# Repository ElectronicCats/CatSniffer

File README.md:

# CatSniffer

<p align=center><b>Where to buy and learn more</b></p>
<p align=center>

</p>

<p align=center>
  
</p>

CatSniffer :smirk_cat: is an original multiprotocol, and multiband board made for sniffing, communicating, and attacking IoT (Internet of Things) devices. It was designed as a highly portable USB stick that integrates the new chips TI CC1352, Semtech SX1262, and an RP2040 for V3 or a Microchip SAMD21E17 for V2.

This board is a swiss army knife for IoT security researchers, developers, and enthusiasts. The board can be used with different types of software including third-party sniffers such as [SmartRF Packet Sniffer](https://www.ti.com/tool/PACKET-SNIFFER), [Sniffle](https://github.com/ElectronicCats/Sniffle), [zigbee2mqtt](https://github.com/Koenkk/zigbee2mqtt), [Z-Stack-firmware](https://github.com/Koenkk/Z-Stack-firmware), [Ubiqua Protocol Analyzer](https://www.ubilogix.com/ubiqua/), [our custom software](https://github.com/ElectronicCats/CatSniffer-Tools), or you can even write your own software for your specific needs.

CatSniffer can operate in 3 different technologies:
* LoRa
* Sub 1 GHz
* 2.4 GHz

This work was inspired by our friend's work [Michael Ossmann](https://twitter.com/michaelossmann) as a tribute to his outstanding job in [Greatscott Gadgets](https://greatscottgadgets.com/), making devices like the YardStick, GreatFET, HackRF, and Ubertooth.

## Versions

The CatSniffer has been evolving since its first release:

- CatSniffer v1.2
- CatSniffer v1.3
- CatSniffer v2.0
- CatSniffer v2.1
- CatSniffer v3.1

We as an pro-open-source companies decided to keep the support for each version, but having in mind that newer versions will have more features than the first versions.

The different firmwares are inside the repository and not in the realese section to keep a propper track of the compiled and source files.

## Protocols
- Thread
- Zigbee
- Bluetooth 5 Low Energy (BLE)
- IEEE 802.15.4g
- 6LoWPAN (IPv6 over Low power Wireless Personal Area Networks)
- Sub 1Ghz and patented systems
- LoRa/LoRaWAN
- Wi-SUN
- Amazon Sidewalk
- mioty®

## Features
- "The SimpleLink™ [CC1352P1F3RGZ](https://www.ti.com/lit/ds/symlink/cc1352p.pdf?ts=1631314674885) device is a multiprotocol and multi-band Sub-1 GHz and 2.4-GHz wireless microcontroller (MCU) supporting Thread, Zigbee®, Bluetooth® 5.2 Low Energy, IEEE 802.15.4g, IPv6-enabled smart objects (6LoWPAN), MIOTY®, Wi-SUN®, proprietary systems".
- CatSniffer uses Microchip SAMD21E17 (V2 or previous) and RP2040 (V3 or later) as a USB-UART bridge to communicate with the CC1352 chip; it's not necessary for a manual driver installation (exceptions could exist).
- Compatible OS: Windows and Linux.
- Auto program through the bootloader from TI CC (as long as it's not disabled in the code). No need for an external programmer, and it can be debugged with cJTAG through the default pin.
- Antenna SMA port for an Antenna of your choice.
- LEDs of general-purpose.
- Reset button for RP2040, SAMD21 & CC1352, Boot of CC1352, and one more for general purpose.

## Wiki and Getting Started

[Getting Started in our Wiki](https://github.com/ElectronicCats/CatSniffer/wiki)

## Firmware Repository
All Catsniffer Firmware has been moved to a different repository, to have a better version control, and issue tracking you will find it here:

https://github.com/ElectronicCats/CatSniffer-Firmware

All catsniffer versions are supported in this repository, you will need to check what version you own and select the proper branch to develop or release for just program your board.

## Software Repository
All Catsniffer Software has been moved to a different repository, to have a better version control, and issue tracking you will find it here:

https://github.com/ElectronicCats/CatSniffer-Tools

## Compatible Software
* [Smart RF Packet Sniffer 2](https://github.com/ElectronicCats/CatSniffer/wiki/06.-Supported-Software#smart-rf-packet-sniffer-2)
* [Wireshark](https://github.com/ElectronicCats/CatSniffer/wiki/06.-Supported-Software#wireshark)
* [pycatsniffer tool (BETA)](https://github.com/ElectronicCats/CatSniffer/wiki/06.-Supported-Software#pycatsniffer-tool)
* [Sniffle](https://github.com/ElectronicCats/CatSniffer/wiki/06.-Supported-Software#sniffle)
* [Ubiqua Protocol Analyzer](https://github.com/ElectronicCats/CatSniffer/wiki/06.-Supported-Software#ubiqua-protocol-analyzer)
* [zigbee2mqtt](https://github.com/Koenkk/zigbee2mqtt)
* [Z-Stack-firmware](https://github.com/Koenkk/Z-Stack-firmware)

## Pre-requisites for building firmware
* Arduino IDE for RP2040 or SAMD21E17
* CCS version: The packet sniffer firmware has been tested with CCS 10.2
* SimpleLink CC13x2 and CC26x2 SDK 
* Python 3

## Note
This kit is designed to allow Product developers to evaluate electronic components, circuit, or software associated with the kit to determine whether to incorporate such items in a finished product and Software developers to write software applications for use with the end product. This kit is a developer product and when assembled may not be resold or otherwise marketed unless all required FCC (or any other local authority) equipment authorizations are first obtained. Operation is subject to the condition that this product not cause harmful interference to licensed radio stations and that this product accept harmful interference.

## Workshops

We have been doing worshops held in different security related events the material avaible is public and can be found [here](https://drive.google.com/drive/folders/1SxkF2-uWVFw2BZa5lym5f42ivyW23bVV)

## How to contribute 
 Contributions are welcome! 

Please read the document  [**Contribution Manual**](https://github.com/ElectronicCats/electroniccats-cla/blob/main/electroniccats-contribution-manual.md)  which will show you how to contribute your changes to the project.

✨ Thanks to all our [contributors](https://github.com/ElectronicCats/CatSniffer/graphs/contributors)! ✨

See [**_Electronic Cats CLA_**](https://github.com/ElectronicCats/electroniccats-cla/blob/main/electroniccats-cla.md) for more information.

See the  [**community code of conduct**](https://github.com/ElectronicCats/electroniccats-cla/blob/main/electroniccats-community-code-of-conduct.md) for a vision of the community we want to build and what we expect from it.

## License

Electronic Cats invests time and resources providing this open source design, please support Electronic Cats and open-source hardware by purchasing products from Electronic Cats!

Designed by Electronic Cats.

Firmware released under an GNU AGPL v3.0 license. See the LICENSE file for more information.

Hardware released under an CERN Open Hardware [Licence v1.2](https://github.com/ElectronicCats/CatSniffer/blob/master/LICENSE.md) See the LICENSE_HARDWARE file for more.
Electronic Cats is a registered trademark, please do not use if you sell these PCBs.

3 April 2021

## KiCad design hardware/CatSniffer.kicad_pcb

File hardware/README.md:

# Hardware

- Schematic
- PCB Gerbers
- Hardware Libraries

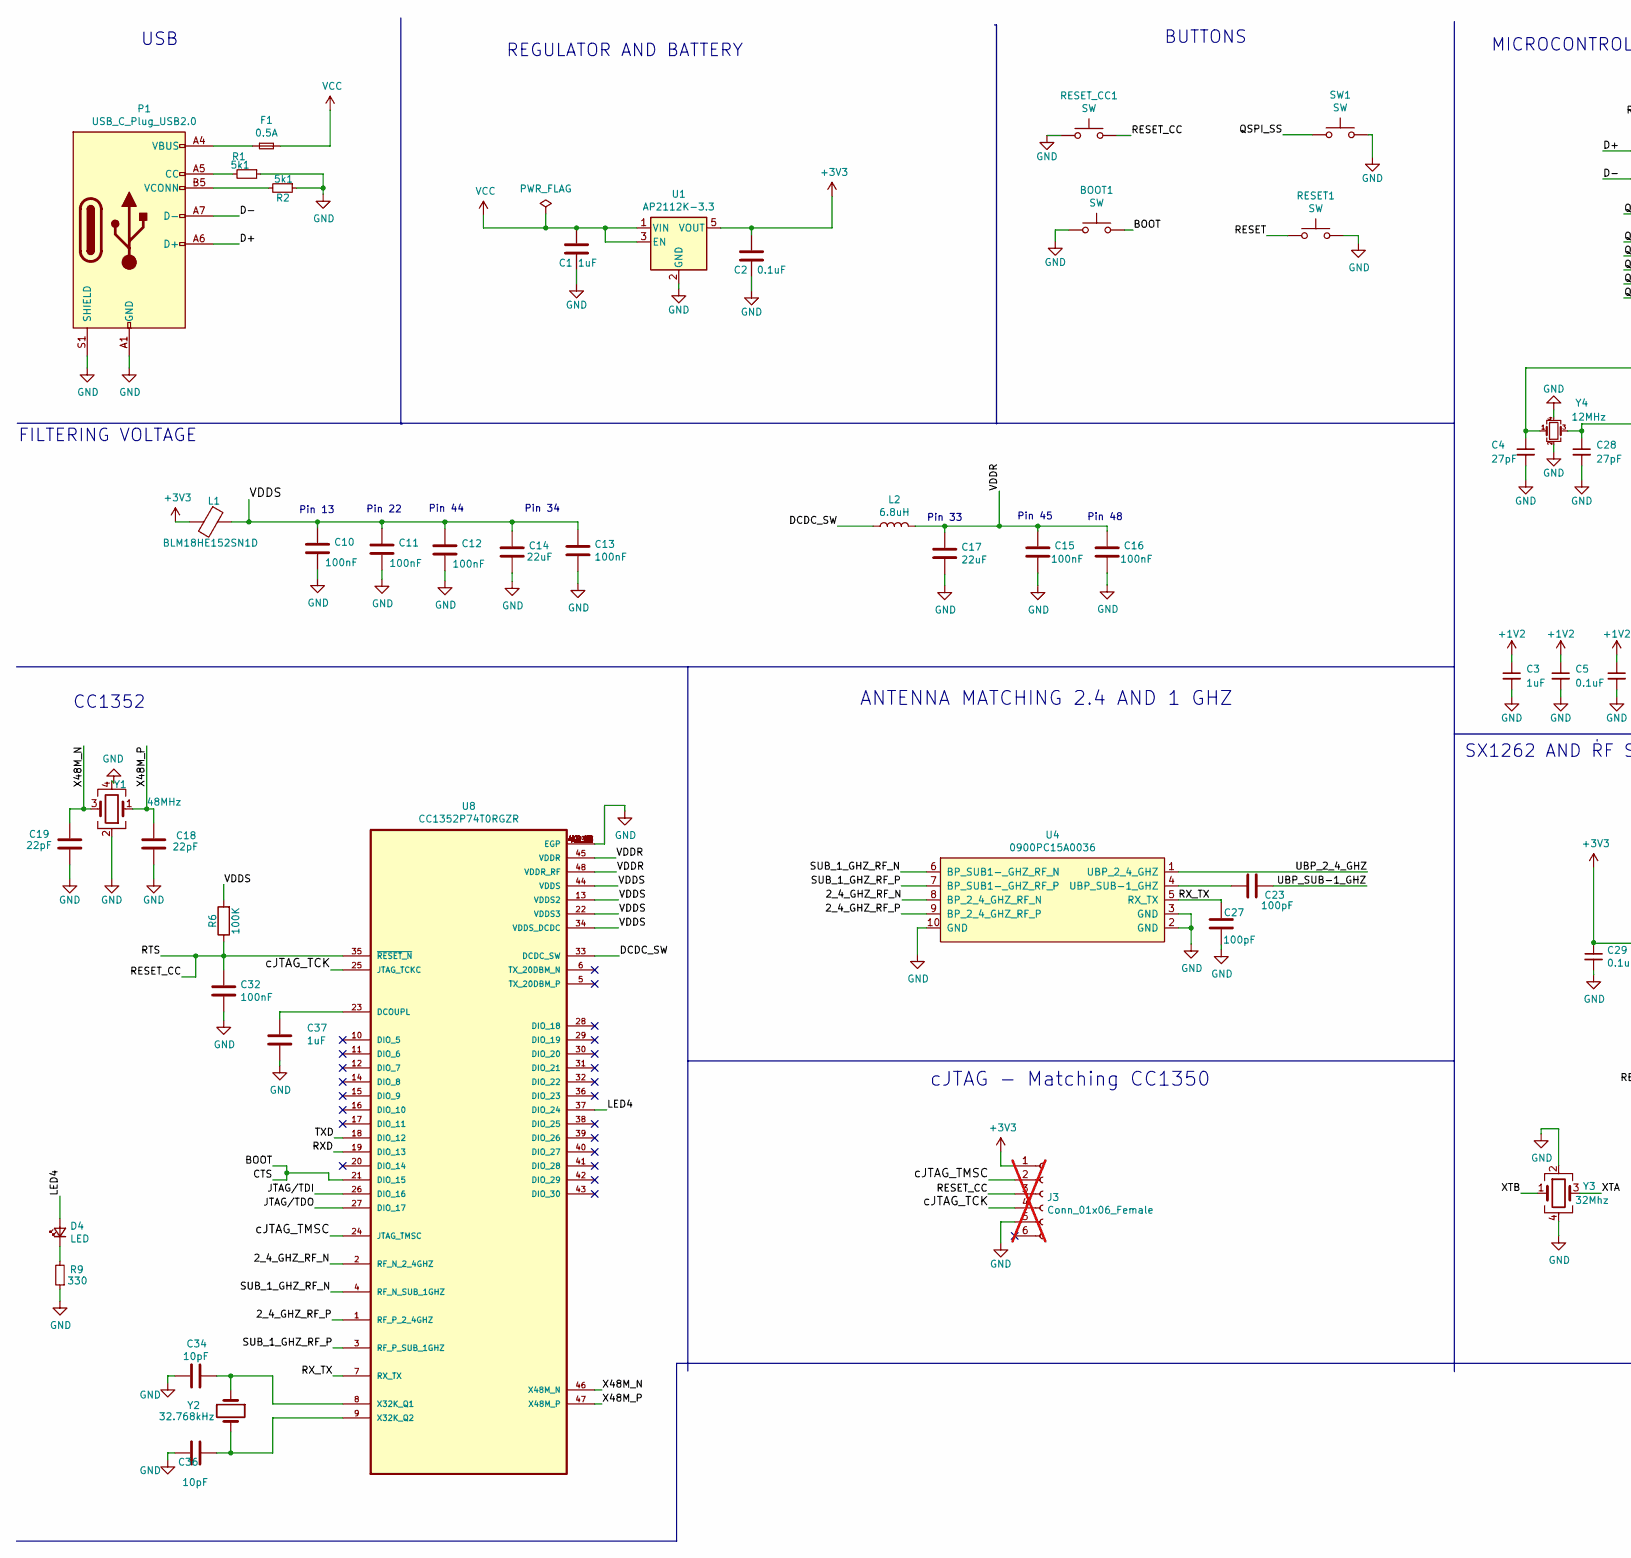
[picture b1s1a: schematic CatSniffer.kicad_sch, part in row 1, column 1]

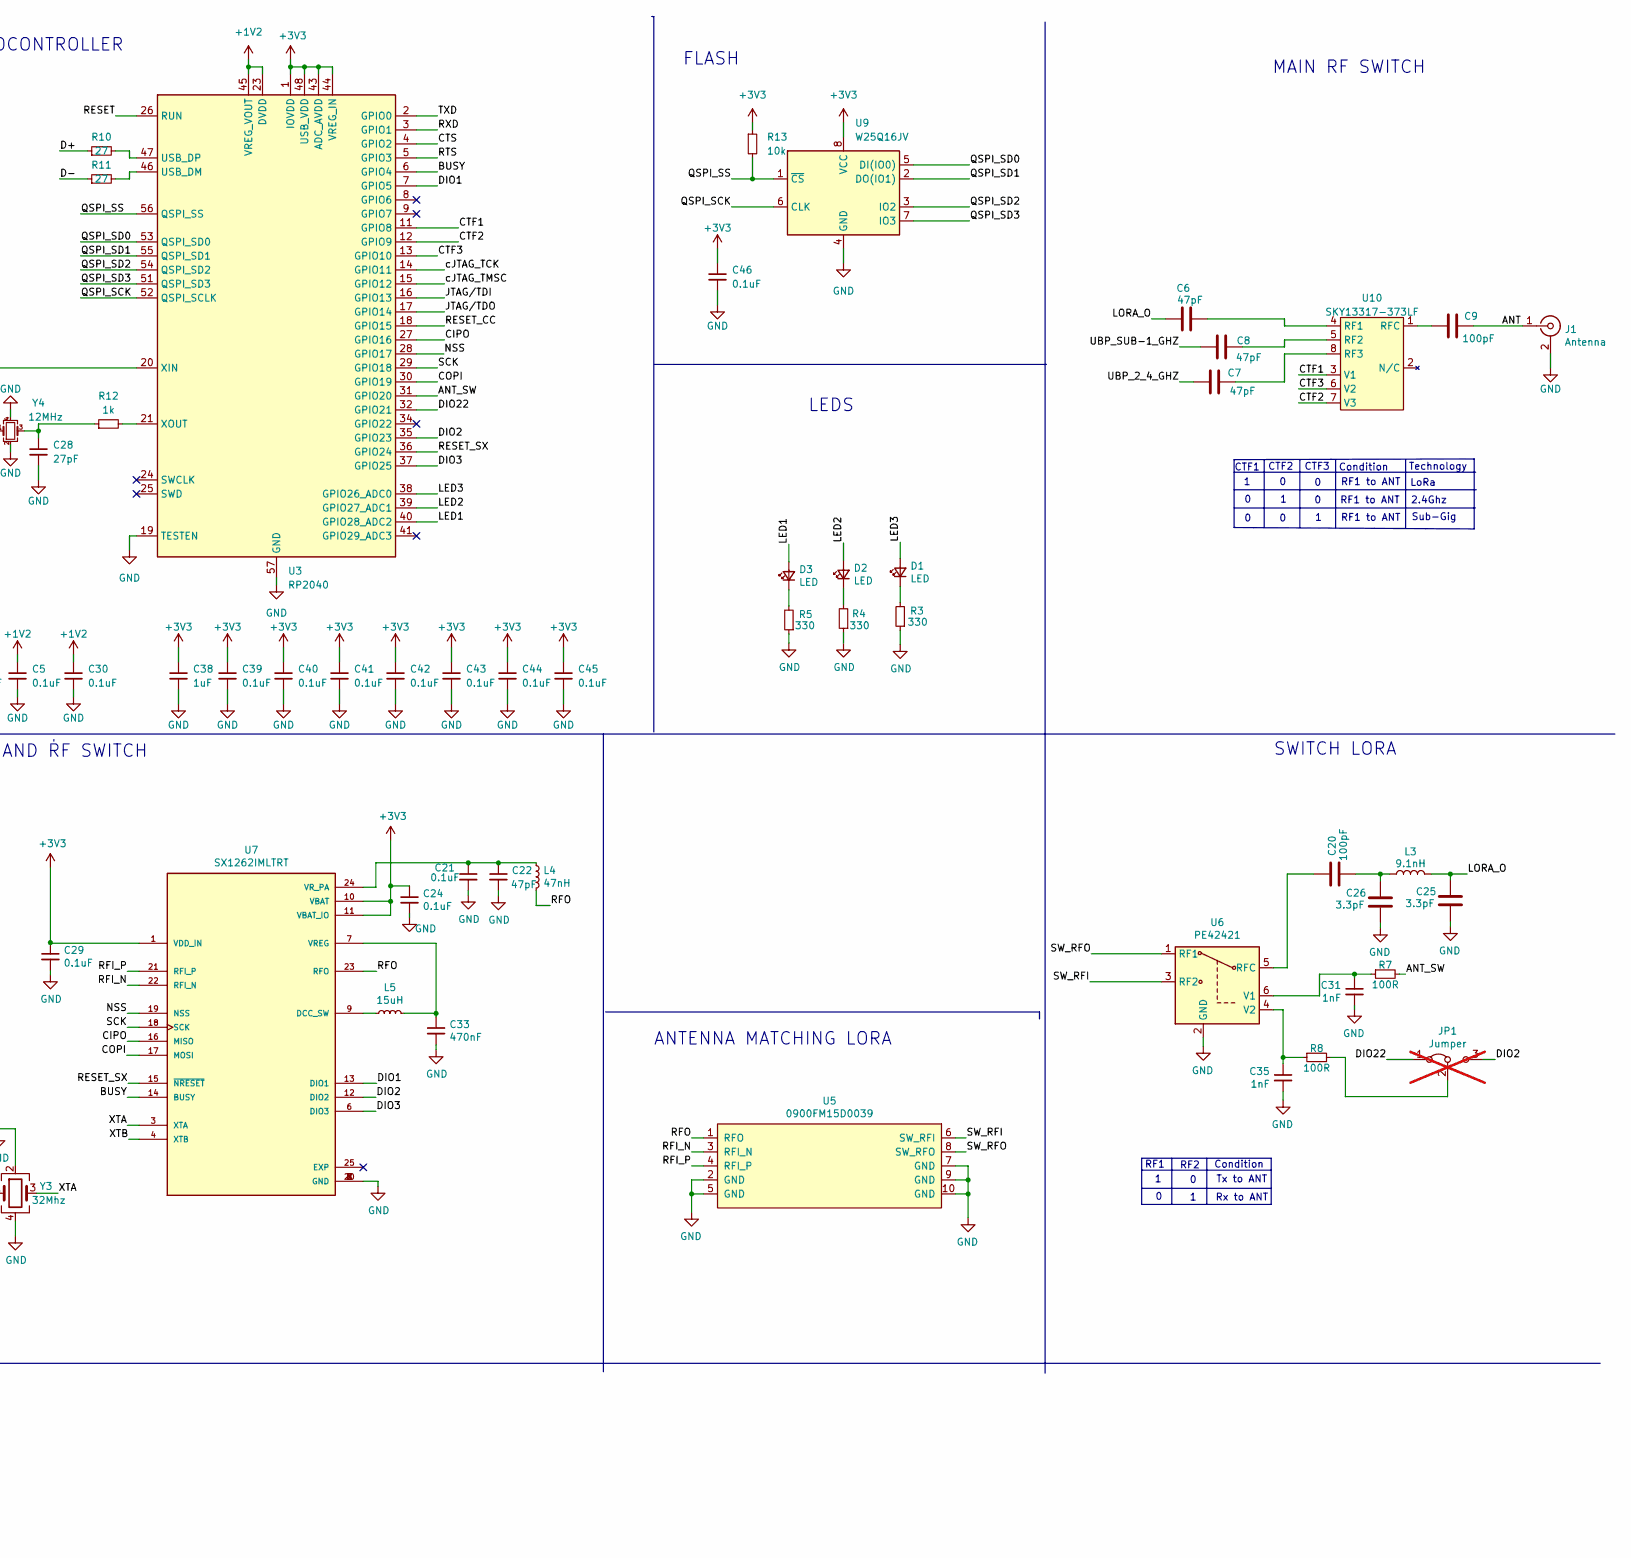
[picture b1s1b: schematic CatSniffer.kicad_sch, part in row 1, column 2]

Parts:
BOOT1: SW; TS1088R02026; LCSC# C455281
C1, C37: 1uF; C_0603_1608Metric; LCSC# C108343
C2, C21, C24, C29: 0.1uF; C_0603_1608Metric; LCSC# C14663
C3, C38: 1uF; C_0402_1005Metric; Mouser# 963-MSRLJ103SB5105MF
C4, C28: 27pF; C_0402_1005Metric; Mouser# 81-GJM1555C1H270FB1D
C5, C30, C39, C40, C41, C42, C43, C44, C45, C46: 0.1uF; C_0402_1005Metric; Mouser# 963-MSAST105SB7104KF
C6, C7, C8, C22: 47pF; C_0603_1608Metric; LCSC# C519486
C9, C20, C23, C27: 100pF; C_0603_1608Metric; LCSC# C14858
C10, C11, C12, C13, C15, C16, C32: 100nF; C_0402_1005Metric; LCSC# C162179
C14, C17: 22uF; C_0603_1608Metric; LCSC# C109447
C18, C19: 22pF; C_0603_1608Metric; LCSC# C170132
C25, C26: 3.3pF; C_0603_1608Metric; LCSC# C162225
C31, C35: 1nF; C_0603_1608Metric; LCSC# C1588
C33: 470nF; C_0603_1608Metric; LCSC# C170149
C34, C36: 10pF; C_0603_1608Metric; LCSC# C472782
D1, D2, D3, D4: LED; LED_0603_1608Metric_Pad1.05x0.95mm_HandSolder; LCSC# C524045
F1: 0.5A; Fuse_0805_2012Metric_Pad1.15x1.40mm_HandSolder; Mouser# 594-MFU0805FF00500P1
J1: Antenna; SMA_EDGE; LCSC# C530661
J3: Conn_01x06_Female; Tag-Connect_TC2030-IDC-NL_2x03_P1.27mm_Vertical; not fitted
JP1: Jumper; SolderJumper-3_P1.3mm_Bridged12_RoundedPad1.0x1.5mm_NumberL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; not fitted
L1: BLM18HE152SN1D; L_0603_1608Metric; Mouser# BLM18HE152SN1D
L2: 6.8uH; L_0603_1608Metric; Mouser# MLZ1608M6R8WT000
L3: 9.1nH; L_0603_1608Metric; LCSC# C395094
L4: 47nH; L_0603_1608Metric; LCSC# C578001
L5: 15uH; L_0603_1608Metric; LCSC# C57838
P1: USB_C_Plug_USB2.0; C393939; LCSC# C709357
R1, R2: 5k1; R_0603_1608Metric; LCSC# C319561
R3, R4, R5, R9: 330; R_0603_1608Metric; LCSC# C408915
R6: 100K; R_0603_1608Metric; LCSC# C179820
R7, R8: 100R; R_0603_1608Metric; LCSC# C700506
R10, R11: 27; R_0402_1005Metric; Mouser# 755-ESR01MZPF27R0
R12: 1k; R_0402_1005Metric; Mouser# 594-MCS0402MD1001DE0
R13: 10k; R_0402_1005Metric; Mouser# 594-MCS04020D1002BE0
RESET1: SW; TS1088R02026; LCSC# C455281
RESET_CC1: SW; TS1088R02026; LCSC# C455281
SW1: SW; TS1088R02026; LCSC# C455281
U1: AP2112K-3.3; SOT-23-5; Mouser# 865-XC6210B332MR-G
U3: RP2040; QFN-56-1EP_7x7mm_P0.4mm_EP3.2x3.2mm; LCSC# C2040
U4: 0900PC15A0036; 0900FM15D0039E; Mouser# 609-0900PC15A0036E
U5: 0900FM15D0039; 0900FM15D0039E; Mouser# 609-0900FM15D0039E
U6: PE42421; SOT-363_SC-70-6; Mouser# 81-PE42421SCAA-Z
U7: SX1262IMLTRT; QFN-24-1EP_4x4mm_P0.5mm_EP2.65x2.65mm; Mouser# 947-SX1262IMLTRT
U8: CC1352P74T0RGZR; VQFN-48-1EP_7x7mm_P0.5mm_EP5.15x5.15mm_ThermalVias; Mouser# 595-CC1352P1F3RGZT
U9: W25Q16JV; W25Q16JVUUIQ; Mouser# 454-W25Q16JVUUIQTR
U10: SKY13317-373LF; LCSC# C129190
Y1: 48MHz; Crystal_SMD_3225-4Pin_3.2x2.5mm; LCSC# C389928
Y2: 32.768kHz; Crystal_SMD_2012-2Pin_2.0x1.2mm; LCSC# C97603
Y3: 32Mhz; Crystal_SMD_2520-4Pin_2.5x2.0mm; LCSC# C255969
Y4: 12MHz; Crystal_SMD_3225-4Pin_3.2x2.5mm; LCSC# C2848217

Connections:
+1V2: C3.1, C5.1, C30.1, U3.23 (DVDD), U3.45 (VREG_VOUT), U3.50 (DVDD)
+3V3: C2.2, C24.1, C29.1, C38.1, C39.1, C40.1, C41.1, C42.1, C43.1, C44.1, C45.1, C46.1, J3.1, L1.2, R13.1, U1.5 (VOUT), U3.1 (IOVDD), U3.10 (IOVDD), U3.22 (IOVDD), U3.33 (IOVDD), U3.42 (IOVDD), U3.43 (ADC_AVDD), U3.44 (VREG_IN), U3.48 (USB_VDD), U3.49 (IOVDD), U7.1 (VDD_IN), U7.10 (VBAT), U7.11 (VBAT_IO), U9.8 (VCC)
/2_4_GHZ_RF_N: U4.8 (BP_2_4_GHZ_RF_N), U8.2 (RF_N_2_4GHZ)
/2_4_GHZ_RF_P: U4.9 (BP_2_4_GHZ_RF_P), U8.1 (RF_P_2_4GHZ)
/ANT: C9.2, J1.1 (In)
/ANT_SW: R7.2, U3.31 (GPIO20)
/BOOT: BOOT1.2, U3.4 (GPIO2), U8.21 (DIO_15)
/BUSY: U3.6 (GPIO4), U7.14 (BUSY)
/CIPO: U3.27 (GPIO16), U7.16 (MISO)
/COPI: U3.30 (GPIO19), U7.17 (MOSI)
/CTF1: U3.11 (GPIO8), U10.3 (V1)
/CTF2: U3.12 (GPIO9), U10.7 (V3)
/CTF3: U3.13 (GPIO10), U10.6 (V2)
/D+: P1.A6 (D+), R10.1
/D-: P1.A7 (D-), R11.1
/DCDC_SW: L2.1, U8.33 (DCDC_SW)
/DIO1: U3.7 (GPIO5), U7.13 (DIO1)
/DIO2: JP1.3 (B), U3.35 (GPIO23), U7.12 (DIO2)
/DIO3: U3.37 (GPIO25), U7.6 (DIO3)
/DIO22: JP1.1 (A), U3.32 (GPIO21)
/JTAG/TDI: U3.16 (GPIO13), U8.26 (DIO_16)
/JTAG/TDO: U3.17 (GPIO14), U8.27 (DIO_17)
/LED1: D3.2 (A), U3.40 (GPIO28_ADC2)
/LED2: D2.2 (A), U3.39 (GPIO27_ADC1)
/LED3: D1.2 (A), U3.38 (GPIO26_ADC0)
/LED4: D4.2 (A), U8.37 (DIO_24)
/LORA_O: C6.1, C25.1, L3.1
/NSS: U3.28 (GPIO17), U7.19 (NSS)
/QSPI_SCK: U3.52 (QSPI_SCLK), U9.6 (CLK)
/QSPI_SD0: U3.53 (QSPI_SD0), U9.5 (DI(IO0))
/QSPI_SD1: U3.55 (QSPI_SD1), U9.2 (DO(IO1))
/QSPI_SD2: U3.54 (QSPI_SD2), U9.3 (IO2)
/QSPI_SD3: U3.51 (QSPI_SD3), U9.7 (IO3)
/QSPI_SS: R13.2, SW1.1, U3.56 (QSPI_SS), U9.1 (~CS)
/RESET: RESET1.1, U3.26 (RUN)
/RESET_CC: C32.1, J3.3, R6.1, RESET_CC1.2, U3.5 (GPIO3), U3.18 (GPIO15), U8.35 (~RESET_N)
/RESET_SX: U3.36 (GPIO24), U7.15 (~NRESET)
/RFI_N: U5.3 (RFI_N), U7.22 (RFI_N)
/RFI_P: U5.4 (RFI_P), U7.21 (RFI_P)
/RFO: L4.2, U5.1 (RFO), U7.23 (RFO)
/RXD: U3.3 (GPIO1), U8.19 (DIO_13)
/RX_TX: C27.2, U4.5 (RX_TX), U8.7 (RX_TX)
/SCK: U3.29 (GPIO18), U7.18 (SCK)
/SUB_1_GHZ_RF_N: U4.6 (BP_SUB1-_GHZ_RF_N), U8.4 (RF_N_SUB_1GHZ)
/SUB_1_GHZ_RF_P: U4.7 (BP_SUB1-_GHZ_RF_P), U8.3 (RF_P_SUB_1GHZ)
/SW_RFI: U5.6 (SW_RFI), U6.3 (RF2)
/SW_RFO: U5.8 (SW_RFO), U6.1 (RF1)
/TXD: U3.2 (GPIO0), U8.18 (DIO_12)
/UBP_2_4_GHZ: C7.1, U4.1 (UBP_2_4_GHZ)
/UBP_SUB-1_GHZ: C8.1, C23.1
/VDDR: C15.1, C16.1, C17.1, L2.2, U8.45 (VDDR), U8.48 (VDDR_RF)
/VDDS: C10.1, C11.1, C12.1, C13.1, C14.1, L1.1, R6.2, U8.13 (VDDS2), U8.22 (VDDS3), U8.34 (VDDS_DCDC), U8.44 (VDDS)
/X48M_N: C19.1, U8.46 (X48M_N), Y1.3
/X48M_P: C18.1, U8.47 (X48M_P), Y1.1
/XTA: U7.3 (XTA), Y3.3
/XTB: U7.4 (XTB), Y3.1
/cJTAG_TCK: J3.4, U3.14 (GPIO11), U8.25 (JTAG_TCKC)
/cJTAG_TMSC: J3.2, U3.15 (GPIO12), U8.24 (JTAG_TMSC)
GND: BOOT1.1, C1.1, C2.1, C3.2, C4.2, C5.2, C10.2, C11.2, C12.2, C13.2, C14.2, C15.2, C16.2, C17.2, C18.2, C19.2, C21.2, C22.2, C24.2, C25.2, C26.2, C27.1, C28.2, C29.2, C30.2, C31.2, C32.2, C33.2, C34.2, C35.2, C36.2, C37.2, C38.2, C39.2, C40.2, C41.2, C42.2, C43.2, C44.2, C45.2, C46.2, J1.2 (Ext), J3.5, P1.A1 (GND), P1.A12 (GND), P1.B1 (GND), P1.B12 (GND), P1.S1 (SHIELD), R1.1, R2.1, R3.1, R4.1, R5.1, R9.1, RESET1.2, RESET_CC1.1, SW1.2, U1.2 (GND), U3.19 (TESTEN), U3.57 (GND), U4.2 (GND), U4.3 (GND), U4.10 (GND), U5.2 (GND), U5.5 (GND), U5.7 (GND), U5.9 (GND), U5.10 (GND), U6.2 (GND), U7.2 (GND), U7.5 (GND), U7.8 (GND), U7.20 (GND), U8.49 (EGP), U8.49_1 (EGP), U8.49_2 (EGP), U8.49_3 (EGP), U8.49_4 (EGP), U8.49_5 (EGP), U8.49_6 (EGP), U8.49_7 (EGP), U8.49_8 (EGP), U8.49_9 (EGP), U8.49_10 (EGP), U8.49_11 (EGP), U8.49_12 (EGP), U8.49_13 (EGP), U8.49_14 (EGP), U8.49_15 (EGP), U8.49_16 (EGP), U8.49_17 (EGP), U8.49_18 (EGP), U8.49_19 (EGP), U8.49_20 (EGP), U8.49_21 (EGP), U9.4 (GND), Y1.2, Y1.4, Y3.2, Y3.4, Y4.2, Y4.4
unnamed: C20.2, C26.1, L3.2
unnamed: C28.1, R12.1, Y4.3
unnamed: D1.1 (K), R3.2
unnamed: D2.1 (K), R4.2
unnamed: D3.1 (K), R5.2
unnamed: D4.1 (K), R9.2
unnamed: F1.1, P1.A4 (VBUS), P1.A9 (VBUS), P1.B4 (VBUS), P1.B9 (VBUS)
unnamed: JP1.2 (C), R8.2
unnamed: P1.A5 (CC), R1.2
unnamed: P1.B5 (VCONN), R2.2
unnamed: R11.2, U3.46 (USB_DM)
unnamed: R10.2, U3.47 (USB_DP)
unnamed: C4.1, U3.20 (XIN), Y4.1
unnamed: R12.2, U3.21 (XOUT)
unnamed: C23.2, U4.4 (UBP_SUB-1_GHZ)
unnamed: C20.1, U6.5 (RFC)
unnamed: C31.1, R7.1, U6.6 (V1)
unnamed: C35.1, R8.1, U6.4 (V2)
unnamed: L5.1, U7.9 (DCC_SW)
unnamed: C33.1, L5.2, U7.7 (VREG)
unnamed: C21.1, C22.1, L4.1, U7.24 (VR_PA)
unnamed: C37.1, U8.23 (DCOUPL)
unnamed: C34.1, U8.8 (X32K_Q1), Y2.1
unnamed: C36.1, U8.9 (X32K_Q2), Y2.2
unnamed: C6.2, U10.4 (RF1)
unnamed: C8.2, U10.5 (RF2)
unnamed: C7.2, U10.8 (RF3)
unnamed: C9.1, U10.1 (RFC)
VCC: C1.2, F1.2, U1.1 (VIN), U1.3 (EN)

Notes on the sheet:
RF1 to ANT
cJTAG - Matching CC1350
Rx to ANT
Pin 48
Pin 33
2.4Ghz
CTF2
REGULATOR AND BATTERY
ANTENNA MATCHING LORA
RF1
SWITCH LORA
ANTENNA MATCHING 2.4 AND 1 GHZ
Pin 34
Pin 45
CTF1
FILTERING VOLTAGE
Condition
Pin 44
Technology
FLASH
Pin 22
Tx to ANT
MAIN RF SWITCH
BUTTONS
Pin 13
CC1352
LoRa
CTF3
Sub-Gig
MICROCONTROLLER
USB
SX1262 AND RF SWITCH
LEDS
RF2

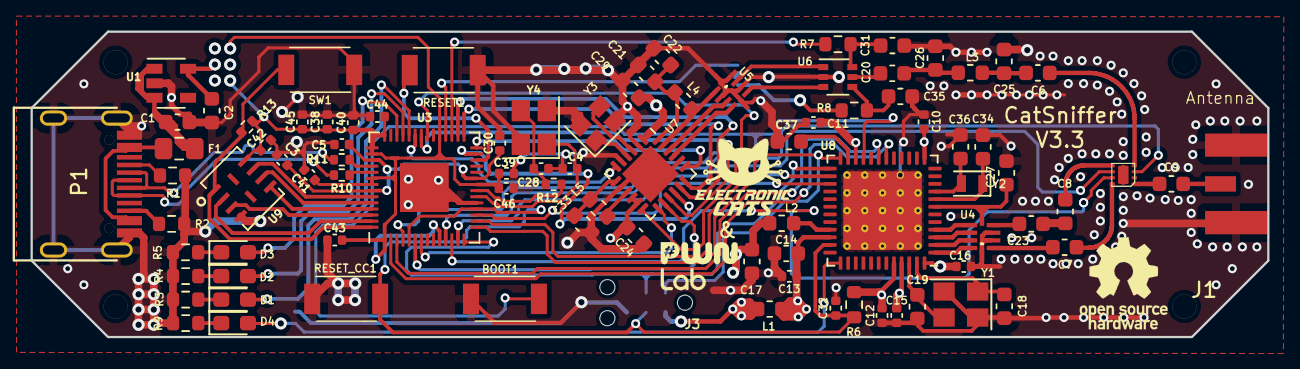
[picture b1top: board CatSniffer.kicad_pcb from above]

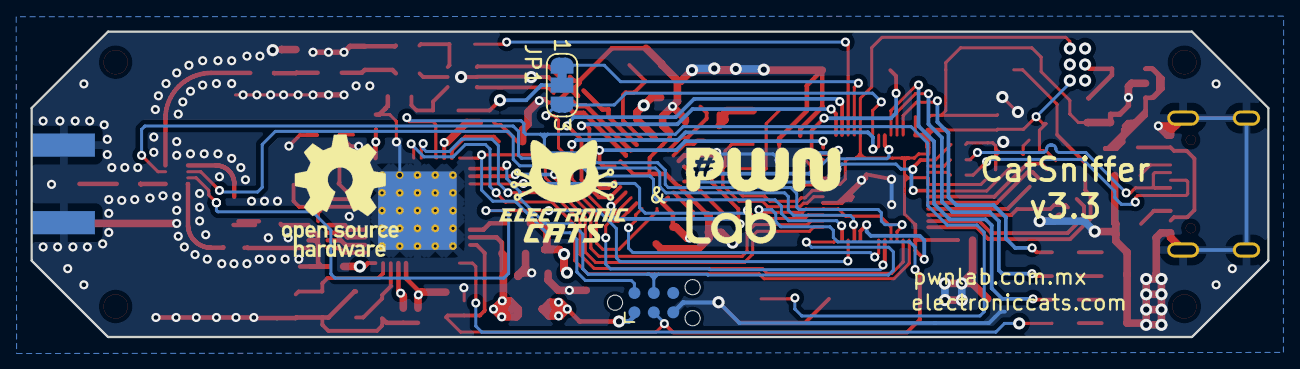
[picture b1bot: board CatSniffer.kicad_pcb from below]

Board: 4 copper layers, 81.0 x 20.0 mm, 90 parts (2 on the bottom side), 88 nets.

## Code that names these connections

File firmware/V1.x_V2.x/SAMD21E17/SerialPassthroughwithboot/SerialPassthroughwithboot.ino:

/*
  SerialPassthrough - Use tool to flash the CC1352 module with the SAMD21E17

  Andres Sabas @ Electronic Cats
  Eduardo Contreras @ Electronic Cats
  Original Creation Date: Jul 10, 2023

  This code is beerware; if you see me (or any other Electronic Cats
  member) at the local, and you've found our code helpful,
  please buy us a round!
  Distributed as-is; no warranty is given.
  
*/

//Pin declaration to enter bootloader mode on CC1352
#define Pin_Reset (1)
#define Pin_Boot (7)
#define Pin_Button (23)
#define LED1 (27)
#define LED2 (28)
#define LED3 (0)
//Mode flag = 1; for bootloader options @ 500000 bauds
//Mode flag = 0; for passthrough @ 921600 bauds
bool MODE_FLAG = 0;
uint8_t LEDs[3]={0,27,28};
int i=0;

unsigned long interval = 0;    // interval to blink LED
unsigned long previousMillis = 0;  // will store last time blink happened
unsigned long baud;

#define CTF1 14
#define CTF2 11
#define CTF3 10

void setup() {
  pinMode(Pin_Button, INPUT_PULLUP);
  pinMode(Pin_Boot, INPUT_PULLUP);
  pinMode(Pin_Reset, OUTPUT);
  pinMode(LED1,OUTPUT);
  pinMode(LED2,OUTPUT);
  pinMode(LED3,OUTPUT);

  //Select mode and speed
  if(!digitalRead(Pin_Boot)){
    interval = 200;
    baud  = 500000;
    MODE_FLAG=1;
  }
  else{
    interval = 1000; 
    baud = 921600;
    MODE_FLAG=0;
  }

  pinMode(Pin_Boot, OUTPUT);

  //Begin Serial ports
  Serial.begin(baud);
  Serial1.begin(baud);

  if(MODE_FLAG){
    //Enter bootloader mode function
    digitalWrite(Pin_Boot, LOW);
    delay(100);
    digitalWrite(Pin_Reset, LOW);
    delay(100);
    digitalWrite(Pin_Reset, HIGH);
    delay(100);
    digitalWrite(Pin_Boot, HIGH);
  }else{
  pinMode(CTF1, OUTPUT);
  pinMode(CTF2, OUTPUT);
  pinMode(CTF3, OUTPUT);
  
  //Switch Radio for 2.4Ghz BLE/WIFI
  digitalWrite(CTF1,  LOW);
  digitalWrite(CTF2,  HIGH);
  digitalWrite(CTF3,  LOW);
  }

  digitalWrite(LED1, 0);
  digitalWrite(LED2, 0);
  digitalWrite(LED3, MODE_FLAG);
}

void loop() {
  //SerialPassthrough
  if (Serial.available()) {      // If anything comes in Serial (USB),
    Serial1.write(Serial.read());   // read it and send it out Serial1 (pins 0 & 1)
  }

  if (Serial1.available()) {     // If anything comes in Serial1 (pins 0 & 1)
    Serial.write(Serial1.read());   // read it and send it out Serial (USB)
  }
  
  if(Serial.baud() != baud){//Check if the Serial port needs a new baud rate
    baud = Serial.baud();
    Serial1.begin(baud);}
  
  if(millis() - previousMillis > interval) {
    previousMillis = millis(); 
    if(MODE_FLAG){
      digitalWrite(LEDs[i], !digitalRead(LEDs[i]));
      i++;
      if(i>2)i=0;
    }else{
      digitalWrite(LED3, !digitalRead(LED3));
    } 
  }
}

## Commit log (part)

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2020-08-15 init schematic
2020-08-15 schematic basic for cc1352
2020-08-15 added Antenna Matching beta
2020-08-15 added switching RF
2020-08-15 Vcc USB
2020-08-15 init schematic for SAMR34
2020-08-16 change labels
2020-08-26 Add sniffer bin CC1352P
2020-08-26 Add source files
2020-08-26 added git modules script bootloader
2020-08-27 update code composer 10
2020-08-27 referencias
2020-08-27 add test connection serial ok
2020-12-08 add cache lib
2021-01-24 update labels
2021-01-24 rescue lib
2021-03-29 addValueCapacitor
2021-03-29 addExternalLoadCapacitors
2021-03-29 changeLoadCapacitors
2021-03-29 connectCrystal48
2021-03-30 changeSch
2021-03-30 addLabelVCC1352
2021-03-30 modifyElementsSch
2021-04-03 update module bsl
2021-04-12 Change to SAMD21E and SX1262 LoRa
2021-04-12 add library SX1262
2021-04-12 add datasheets
2021-04-20 init SerialPassthrough
2021-04-21 switch RF
2021-04-21 addAntenna
2021-04-21 selectCapacitors
2021-04-22 addUSBC
2021-04-22 addComponents&footprints
2021-04-22 Rename project
2021-04-23 completeComponents&footprints
2021-04-23 addLEDSAMD21
2021-04-23 fixFootprint
2021-04-23 fixPinNumberComponent
2021-04-26 uploadFloorplan
2021-04-26 fixSWDforSAMD21E
2021-04-26 updateSWDfootprint
2021-04-27 Modify schematic for better reading
2021-04-27 fixSAMDsch
2021-04-27 add line
2021-04-27 updateFirmware
2021-04-27 Add Prerequisites
2021-04-28 enable bootloader mode
2021-04-28 Update Prerequisites
2021-04-28 Add Sniffle module
2021-04-28 addResistorReset
2021-04-28 addSAMDfootprint
2021-04-29 addButtonResetCC1352
2021-04-29 addFirmwareFolder
2021-05-01 FloorplanInProgress
2021-05-03 BatteryRemove
2021-05-03 fix source for cc1352
2021-05-03 placeSX,CC&SAMD
2021-05-04 update floorplan
2021-05-04 add 3D
2021-05-04 fixCrossSignals
2021-05-04 addUserSwitch
2021-05-04 floorPlan
2021-05-05 updateBoom
2021-05-05 SchChanges&fixLabels
2021-05-05 newFloorPlanInProgress
2021-05-06 NewFloorPlan
2021-05-07 updated floorplan
2021-05-07 RoutingInProgress
2021-05-10 RoutingGND&VCClayers
2021-05-10 RoutingSPIinProgress
2021-05-11 RoutingCTFInProgress
2021-05-11 RoutingComplete
2021-05-11 PCBReadytoRevision
2021-05-11 udate traces and sch to best routes
2021-05-11 update trace
2021-05-12 updatePCB
2021-05-13 updateTraces
2021-05-16 update RF with correct impedance
2021-05-16 update impedance information
2021-05-17 update RF traces
2021-05-18 SerialPassThroughInProgress
2021-05-19 addSerialPassThrough
2021-05-19 updateSerialPassThrough
2021-05-21 addZigbee2MQTTcompatibility
2021-05-25 removeUnusedVariables
2021-05-25 addCommentstoCode
2021-05-25 rename paths
2021-05-25 Remove script test
2021-06-10 fixDecopulingCap
2021-06-10 updateCrystalsCap
2021-06-10 updateCC1352cJTAG
2021-06-10 fixLabels
2021-06-10 updateBOM
2021-06-10 NRoutingCC13inProgress
2021-06-11 update info RF switch
2021-06-11 add LoRa example
2021-06-14 changeCap0402
2021-06-14 fixVDDRLabel
2021-06-14 changeLabelsSize
2021-06-14 updateRouteDCDC_SW
2021-06-14 removeCapCrystalSX
2021-06-14 updateSX1262PCB
2021-06-14 fixWidthVDDStrace
2021-06-14 add logos
2021-06-17 updatePCBvias
2021-06-17 fixPCBVias
2021-06-18 fix ground planes
2021-06-21 addCC1352RHexFile
2021-06-21 add groudn connection
2021-07-02 DRC clean
2021-07-08 fixRX/TXCC1352
2021-07-08 update traces RX/TX
2021-07-09 v1.2 production
2021-07-16 updateCC1352hex
2021-07-16 addSniffer_fw
2021-07-16 updateSniffer_fw
2021-07-16 updateSMF_Fw
2021-07-19 rename project kicad
2021-07-23 Update firmware, remove fimware for other chips
2021-07-23 update submodule
2021-07-23 Update description examples
2021-07-26 add serial for Sniffle
2021-07-30 Typos
2021-07-30 Protocol list style
2021-07-30 Feature update
2021-08-01 Update Sniffle for ElectronicCats version
2021-08-02 Screenshots para documentacion en espanol
2021-08-02 Mueve screenshots al wiki
2021-08-02 DoS LoRa
2021-08-02 Some LoRa attacks
2021-08-02 Adds bit flipping paper
2021-08-02 6LoWPAN attacks
2021-08-02 EM Analysis in the IoT Context: Lessons Learned from an Attack on Thread
2021-08-02 IEEE 802.15.4g attacks
2021-08-02 Agrega informacion del switch
2021-08-02 firmware folder
2021-08-02 Mueve a docs
2021-08-02 Corrige version de SmartRF Packet Sniffer
2021-08-04 add submodule thread cc1352
2021-08-04 Fixes typo in product name
2021-08-04 Fixes format
2021-08-04 Translates readme to english
2021-08-13 update3Dmodel
2021-08-17 Basic case for CatSniffer
2021-08-20 ChngCC1352P
2021-08-21 Moves firmware to fw folder
2021-08-21 Update .gitmodules
    Moves submodules to fw folder
2021-08-21 Adds info about switch
2021-08-26 case mamalon v1
2021-08-26 basic case in folder
2021-09-11 Removes sniffle as files
2021-09-11 Adds sniffle as a submodule
2021-09-13 Cambios de readme
2021-09-13 Adds image with buttons reference
2021-09-13 Faltaba una coma
2021-09-25 Syncs readme
2021-09-25 Removes sdk versions
2021-09-25 Comma
2021-10-21 addNewFirmwareLoRa
2021-10-22 Adds SX126 examples to firmware folder
2021-11-07 remove duplicate submodule
2022-02-01 UpdateKicad6
2022-02-02 removeZIPfiles
2022-03-19 Fixes typo
2022-03-23 add gitignore
2022-03-23 add sch PDF
2022-03-23 erase extra files
2022-05-04 update version
2022-05-25 Syscfg Template
    The .syscfg contains the settings of the DIO of the CatSniffer.
2022-08-02 Syscfg Template for Beacon (BLE)
2022-09-29 Create stale config
2022-09-30 ISSUE_TEMPLATE added
2022-10-05 add LoraCatSniffer CLI
2022-11-18 Update example LoRa
2022-12-15 Init RP2040
2022-12-16 Change RP2040
2022-12-17 Add boot rp2040, add CTS and RTS serial
2022-12-19 BOM and schematic
2022-12-19 change of components rp2040
2022-12-20 change to rp2040
2022-12-21 Initial routing
2022-12-22 CC1353 class
2022-12-22 routing rp2040
2022-12-26 For revision
2022-12-27 schematic correction
2022-12-28 add class Packet, test callback
2022-12-28 shcematic correction and labels
2023-01-02 receive threading running
2023-01-02 packets (hex) in console
2023-01-02 extract frames
2023-01-09 update traces enhaced ground fix GND in. layer
2023-01-11 Change footprint
2023-01-11 extras
2023-01-11 RFSW8006QTR7 change footprint
2023-01-13 Edit silkscreen
2023-01-19 update_bom
2023-01-19 update rp2040
2023-01-19 remove gitmodules
2023-01-19 add pcap classes
2023-01-24 Add remaining functions
2023-01-26 dissect timestamp, payload
2023-02-01 set channel for BLE (37-39)
2023-02-02 added README
2023-02-02 corrections in README
2023-02-14 fix BOM and add 3d components
2023-02-15 Update README.md
    commas and periods are added
2023-03-14 Fix README errors
2023-04-03 fix serigraphy
2023-04-03 fix serigraphy "c14"
2023-04-22 add pico firmware
2023-05-22 fix SPI RF port
2023-05-22 Routed CIPO, NSS, SCK, COPI, CTF1 and CTF2
2023-05-31 add components replacements and fix "antena" serigraphy
2023-06-06 add serigraphy version to "V3.1"
2023-06-23 update RF switch connected to microcontroller
2023-06-23 fix serigraphy version v3.2 to v3.1
2023-06-23 edit footprint of U5 & U4 for better view of polarity
2023-06-29 Update README.md
    Added to the description that the new version is RP2040
2023-07-09 AirtagSpoofer firmware
2023-07-09 Syncs main repo
2023-07-11 modify serialpassthroughwithboot, for multiple functionalities
2023-07-11 add LED animation for upload
2023-07-11 Airtag scanner firmware
2023-07-20 update examples SAMD21 and RP2040
2023-07-21 Transmitting packet RP2040
2023-07-22 update script to work with cc1352P7
2023-08-01 update v1.x_2.x and v3.x folders
2023-08-01 move subfolders
2023-08-01 add TX/RX control LoRa
2023-08-01 add serialWithBoot RP2040
2023-08-01 update serial example
2023-08-02 update serialPassthrough RP2040
2023-08-02 add CC1352P7 examples
2023-09-07 cc1352P7 sniffer firmware
2023-09-07 fimrware uf2 for rp2040
2023-09-08 add sniffle firmware
2023-09-13 normalize bauds for serialpasstrhough
2023-09-13 add firmware README
2023-09-13 Add notes on README
2023-10-27 Add RFSW to SerialPassthroughwithboot in V1 and V2
2023-10-31 Add RFSW to SerialPassthroughwithboot in V3
2023-11-14 update LoRa Scripts
2023-11-14 update LoRa-CLI
2023-11-17 update cli examples
2023-11-17 erase comment
2023-11-22 fix lower case hex input, fix set_tx_ascii()
2023-11-22 fix lower set tx ascii samd21
2023-11-22 rename LoRaCatsnifer to LoRa-CLI
2023-12-07 update precompiled SerialPassthrough
2023-12-20 Update README.md
    Agregar imagen de producto, link a wiki con imagen y link a tienda con imagen
2023-12-20 Update README.md
    Ahora si ya estan todas las imagenes en GitHub. Se agregaró la imagen de la versión 3 de la tarjeta, la imagen con liga a la tienda y la imagen con liga a la wiki. También modifique los protocolos y 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
2023-12-24 Added folder for talks and workshops
2024-01-03 added case 500 kz to bw to sniff downlinks
2024-01-15 add STEP file
2024-01-18 Enlarged U4, U5 and update PCB
2024-01-21 remove all software related
2024-01-25 feature: added set_inv_iq function
2024-03-20 feat (docs) : HackGDL Conference
    - Add Docs from the conference
    - Link to the media files
    - Update Readme conference list
2024-03-25 feat(docs): Update conference
    - Update video links
    - Update table of content
2024-03-27 feat(docs) : How contrib
    - Show how PyCatSniffer works and how contribute
2024-04-09 feat(docs): Update README.md
2024-04-24 feat(docs):Update README.md
    Add distributor store button
2024-04-24 fix(docs): emoji markdown correction
2024-04-26 doc(main): How to contribute
    - Update the description with the lasted version of our How to contribute document
2024-06-07 feat: Add doc
    - Add more information about "how to"
2024-06-24 Adds BH Asia 2024 Arsenal Lab
2024-06-25 Agrega case con leyenda 'Catsniffer'
2024-07-08 feat: change LICENSE
2024-07-08 feat: remove license firmware
2024-08-14 fix: Update README.md links
2024-08-19 fix: broken links
2024-08-19 fix: images and format
2024-09-05 feat(Hw): Update labels
2024-10-21 feat: Add Zigbee PoC
    - MITM
    - Targeting and Jamming
2024-10-22 feat: Add Offset
2024-10-22 feat: Add PCAPS examples
2024-10-28 fix: typo
2024-10-29 feat: Add BLE PCAPS
2025-01-15 fix(Hw):Update_DNP_Parts
2025-02-16 Update REWARDS.md
    Missing last sentence.
2025-04-03 feat(hw): new case
2025-08-16 Create Catsniffer-Setup-and-Firmware-Strategy.ipynb
    Agrega el primer notebook que demuestra como cargar y probar un firmware.
2026-02-12 feat(HW):CC1352P74T0RGZR_Updated
